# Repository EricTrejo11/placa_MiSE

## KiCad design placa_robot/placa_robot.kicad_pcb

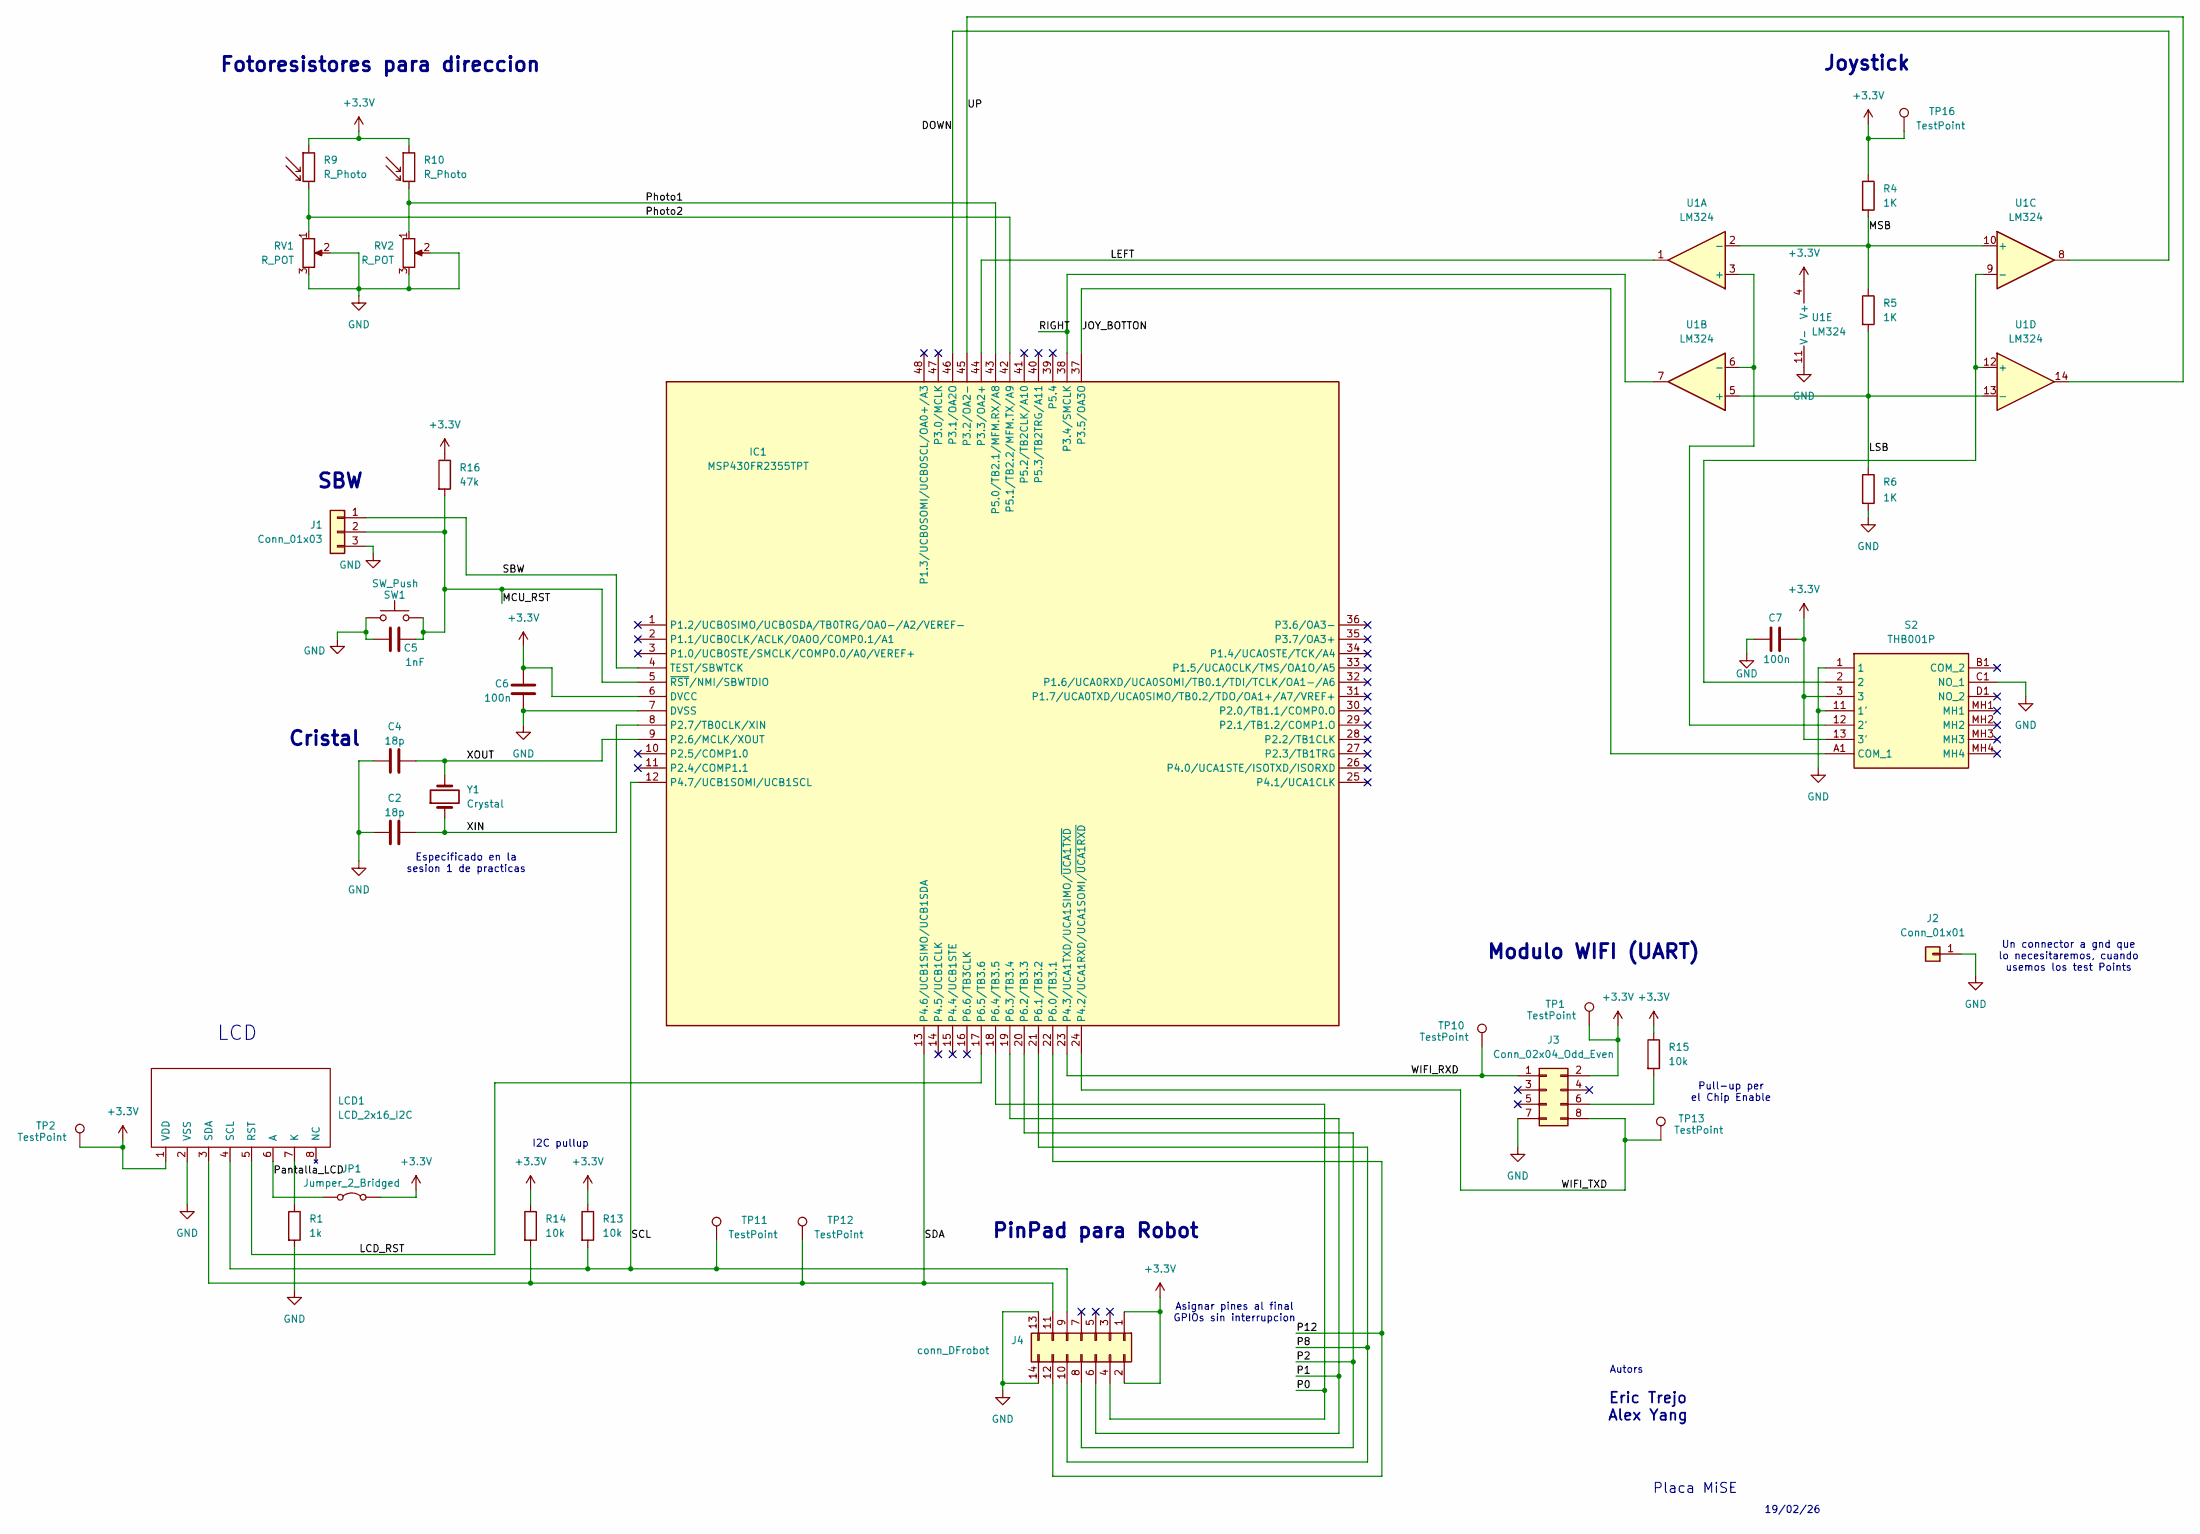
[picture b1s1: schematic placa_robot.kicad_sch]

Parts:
C2, C4: 18p; C_0805_2012Metric_Pad1.18x1.45mm_HandSolder
C5: 1nF; C_0805_2012Metric_Pad1.18x1.45mm_HandSolder
C6, C7: 100n; C_0805_2012Metric_Pad1.18x1.45mm_HandSolder
IC1: MSP430FR2355TPT; QFP50P900X900X160-48N; Manufacturer_Part_Number MSP430FR2355TPT; Mouser Part Number 595-MSP430FR2355TPT
J1: Conn_01x03; PinHeader_1x03_P2.54mm_Vertical
J2: Conn_01x01; PinHeader_1x01_P2.54mm_Vertical
J3: Conn_02x04_Odd_Even; PinHeader_2x04_P2.54mm_Vertical
J4: conn_DFrobot
JP1: Jumper_2_Bridged; TestPoint_2Pads_Pitch2.54mm_Drill0.8mm
LCD1: LCD_2x16_I2C; LCD_2x16_I2C(Midas)
R1: 1k; R_0805_2012Metric_Pad1.20x1.40mm_HandSolder
R4, R5, R6: 1K; R_0805_2012Metric_Pad1.20x1.40mm_HandSolder
R9, R10: R_Photo; PinHeader_1x02_P2.54mm_Vertical
R13, R14, R15: 10k; R_0805_2012Metric_Pad1.20x1.40mm_HandSolder
R16: 47k; R_0805_2012Metric_Pad1.20x1.40mm_HandSolder
RV1, RV2: R_POT; Trimmer_MiSE
S2: THB001P; Manufacturer_Part_Number THB001P; Mouser Part Number 611-THB001P
SW1: SW_Push; SW_PUSH_6mm
TP1, TP2, TP10, TP11, TP12, TP13, TP16: TestPoint; PinHeader_1x01_P2.54mm_Vertical
U1: LM324; SOIC-14_3.9x8.7mm_P1.27mm
Y1: Crystal; Crystal_DS26_D2.0mm_L6.0mm_Horizontal

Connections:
+3.3V: C6.2, C7.1, IC1.6 (DVCC), J3.2, J4.1, J4.2, JP1.2 (B), LCD1.1 (VDD), R4.1, R9.1, R10.1, R13.1, R14.1, R15.1, R16.1, S2.3, S2.13 (3'), TP1.1, TP2.1, TP16.1, U1.4 (V+)
/DOWN: IC1.46 (P3.1/OA2O), U1.8
/JOY_BOTTON: IC1.37 (P3.5/OA3O), S2.A1 (COM_1)
/LCD_RST: IC1.17 (P6.5/TB3.6), LCD1.5 (RST)
/LEFT: IC1.44 (P3.3/OA2+), U1.1
/LSB: R5.2, R6.1, U1.5 (+), U1.13 (-)
/MCU_RST: C5.2, IC1.5 (~RST/NMI/SBWTDIO), J1.2, R16.2, SW1.2
/MSB: R4.2, R5.1, U1.2 (-), U1.10 (+)
/P0: IC1.18 (P6.4/TB3.5), J4.4
/P1: IC1.19 (P6.3/TB3.4), J4.6
/P2: IC1.20 (P6.2/TB3.3), J4.8
/P8: IC1.21 (P6.1/TB3.2), J4.10
/P12: IC1.22 (P6.0/TB3.1), J4.12
/Pantalla_LCD: JP1.1 (A), LCD1.6 (A)
/Photo1: IC1.43 (P5.0/TB2.1/MFM.RX/A8), R10.2, RV2.1
/Photo2: IC1.42 (P5.1/TB2.2/MFM.TX/A9), R9.2, RV1.1
/RIGHT: IC1.38 (P3.4/SMCLK), U1.7
/SBW: IC1.4 (TEST/SBWTCK), J1.1
/SCL: IC1.12 (P4.7/UCB1SOMI/UCB1SCL), J4.9, LCD1.4 (SCL), R13.2, TP11.1; also elsewhere on the board
/SDA: IC1.13 (P4.6/UCB1SIMO/UCB1SDA), J4.11, LCD1.3 (SDA), R14.2, TP12.1; also elsewhere on the board
/UP: IC1.45 (P3.2/OA2-), U1.14
/WIFI_RXD: IC1.23 (P4.3/UCA1TXD/UCA1SIMO/~UCA1TXD), J3.1, TP10.1
/WIFI_TXD: IC1.24 (P4.2/UCA1RXD/UCA1SOMI/~UCA1RXD), J3.8, TP13.1
/XIN: C2.2, IC1.8 (P2.7/TB0CLK/XIN), Y1.1
/XOUT: C4.2, IC1.9 (P2.6/MCLK/XOUT), Y1.2
GND: C2.1, C4.1, C5.1, C6.1, C7.2, IC1.7 (DVSS), J1.3, J2.1, J3.7, J4.13, J4.14, LCD1.2 (VSS), R1.2, R6.2, RV1.2, RV1.3, RV2.2, RV2.3, S2.1, S2.11 (1'), S2.C1 (NO_1), SW1.1, U1.11 (V-)
unnamed: J3.6, R15.2
unnamed: LCD1.7 (K), R1.1
unnamed: S2.12 (2'), U1.3 (+), U1.6 (-)
unnamed: S2.2, U1.9 (-), U1.12 (+)

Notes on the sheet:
Fotoresistores para direccion
PinPad para Robot
I2C pullup
Joystick
Placa MiSE
Eric Trejo Alex Yang
Pull-up per el Chip Enable
19/02/26
Asignar pines al final GPIOs sin interrupcion
LCD
Autors
Un connector a gnd que lo necesitaremos, cuando usemos los test Points
Especificado en la sesion 1 de practicas
SBW
Cristal
Modulo WIFI (UART)

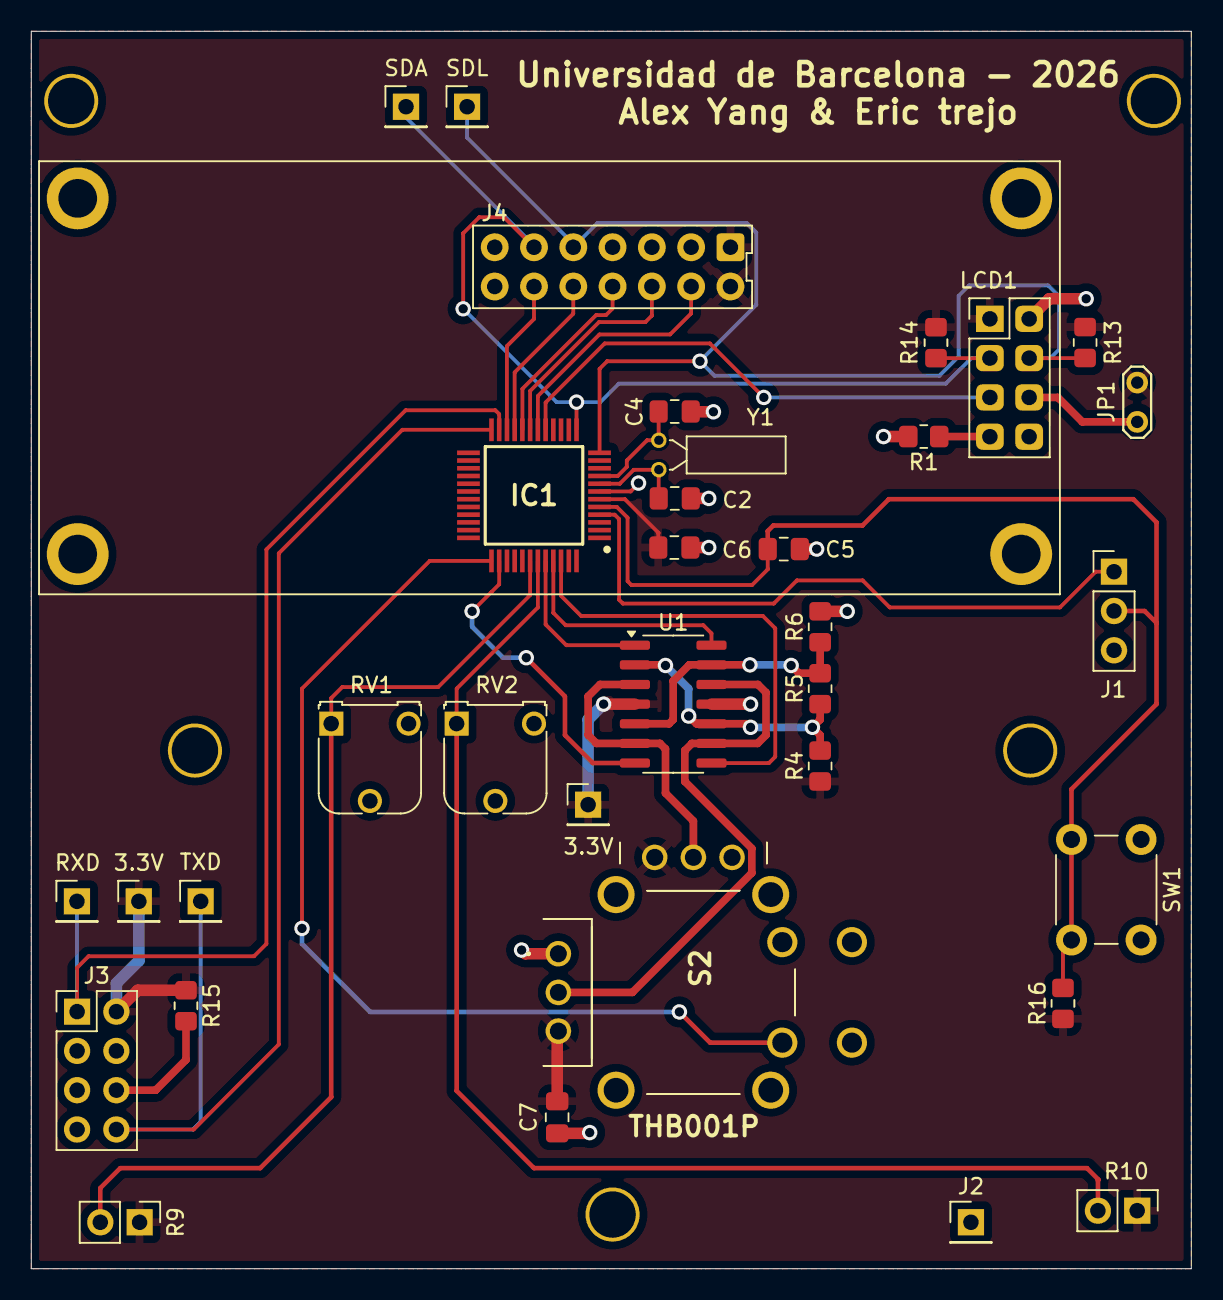
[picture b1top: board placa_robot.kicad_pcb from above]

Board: 2 copper layers, 75.0 x 80.0 mm, 34 parts (0 on the bottom side), 30 nets.

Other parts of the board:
SDA: TestPoint; PinHeader_1x01_P2.54mm_Vertical
SDL: TestPoint; PinHeader_1x01_P2.54mm_Vertical

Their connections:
/SCL: SDL.1; also elsewhere on the board
/SDA: SDA.1; also elsewhere on the board

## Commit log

2026-02-26 Prueba
2026-02-26 agrandar pagina
2026-02-26 Joystick
2026-02-26 Cambios Joystick
2026-02-26 merge
2026-02-26 Fotoresistores
2026-03-05 Sensor_ultraso
2026-03-05 test_point
2026-03-05 Conn Robot y pines
2026-03-05 SBW reset
2026-03-05 Connectar Joystick
2026-03-05 test point
2026-03-05 hola
2026-03-05 wifi
2026-03-05 Cambio joystick
2026-03-05 Netclasss
2026-03-05 Poner no connectar
2026-03-07 Cambiar netclass
2026-03-11 Revert "Merge branch 'main' of https://github.com/EricTrejo11/placa_MiSE"
    This reverts commit 0f96c01b1f59f32d3d821f83131687b0fcfbfda1, reversing
    changes made to 84e450eab26eee0b6b5e6e2c24201ddf691c19bf.
2026-03-11 Revert "Cambiar netclass"
    This reverts commit 84e450eab26eee0b6b5e6e2c24201ddf691c19bf.
2026-03-11 Huellas done
2026-03-11 Nombres asignados, layout started
2026-03-11 reglas de diseño fijadas y clases de red
2026-03-11 Medidas
2026-03-11 Cambio netclass
2026-03-11 mover una cosa
2026-03-11 Layout sin micro
2026-03-11 Layout
2026-03-11 Progreso actual Layout y errores
2026-03-11 Cambios layout
2026-03-11 pequeño cambio
2026-03-11 cambio menor
2026-03-12 cambio layout
2026-03-12 Desacoplos y limitador
2026-03-12 Errores layout
2026-03-12 Placa acabada
2026-03-12 Serigrafia y testpoints colocados
2026-03-14 Arreglos varios
2026-03-14 Cable layout
2026-03-14 Modificar SBW layout
2026-03-15 gerbers
2026-03-15 entrega
